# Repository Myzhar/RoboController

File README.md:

RoboController
==============

This project contains the software and firmware developed for RoboController v2 board: http://www.tuttoelettronica.org/?p=455

RobotController v2 is a board created to perform advanced motor control when you need RealTime control of two motors with encoder feedback. 

The RoboController v2 board is used to control MyzharBot robot: http://www.robot-home.it

MODULES
-------

* **HLU** (**H**igh **L**evel **U**nit): the **HLU** folder contains the High Level software, all the software that runs on a CPU (PC, embedded boards, mobile devices)
* **LLU** (**L**ow **L**evel **U**nit): the **LLU** folder contains the Low Level software, "the firmware", that runs on a MCU (Motor control board, sensor boards, IMU)

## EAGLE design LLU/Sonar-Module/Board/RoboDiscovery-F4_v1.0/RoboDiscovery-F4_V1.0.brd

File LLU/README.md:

LLU
===

LOW LEVEL UNIT
--------------

LLU folder contains the Low Level software, all the software that runs on a board powered by a MCU:

* **CPU**: contains the FW code for RoboController v2 board 
* **Sonar-Module**: contains the FW code for STm32F4-Discovery to be suited on RoboDiscovery carrier board

DEVELOPMENT SOFTWARE
--------------------

**Microchip - RoboController v2**
To compile the Firmware to be deployed on RoboController board you need a Microchip programmer (PicKit 3 or ICD 3 are highly suggested) and you need to download the latest version of MPLABX IDE and XC16 from Microchip: https://www.microchip.com/pagehandler/en-us/family/mplabx/

**STm32F4-Discovery**
The Firmware is based on the newest STm32Cube library and it is configured using STm32CubeMX tool.
You will find any further information on www.robodiscovery.com

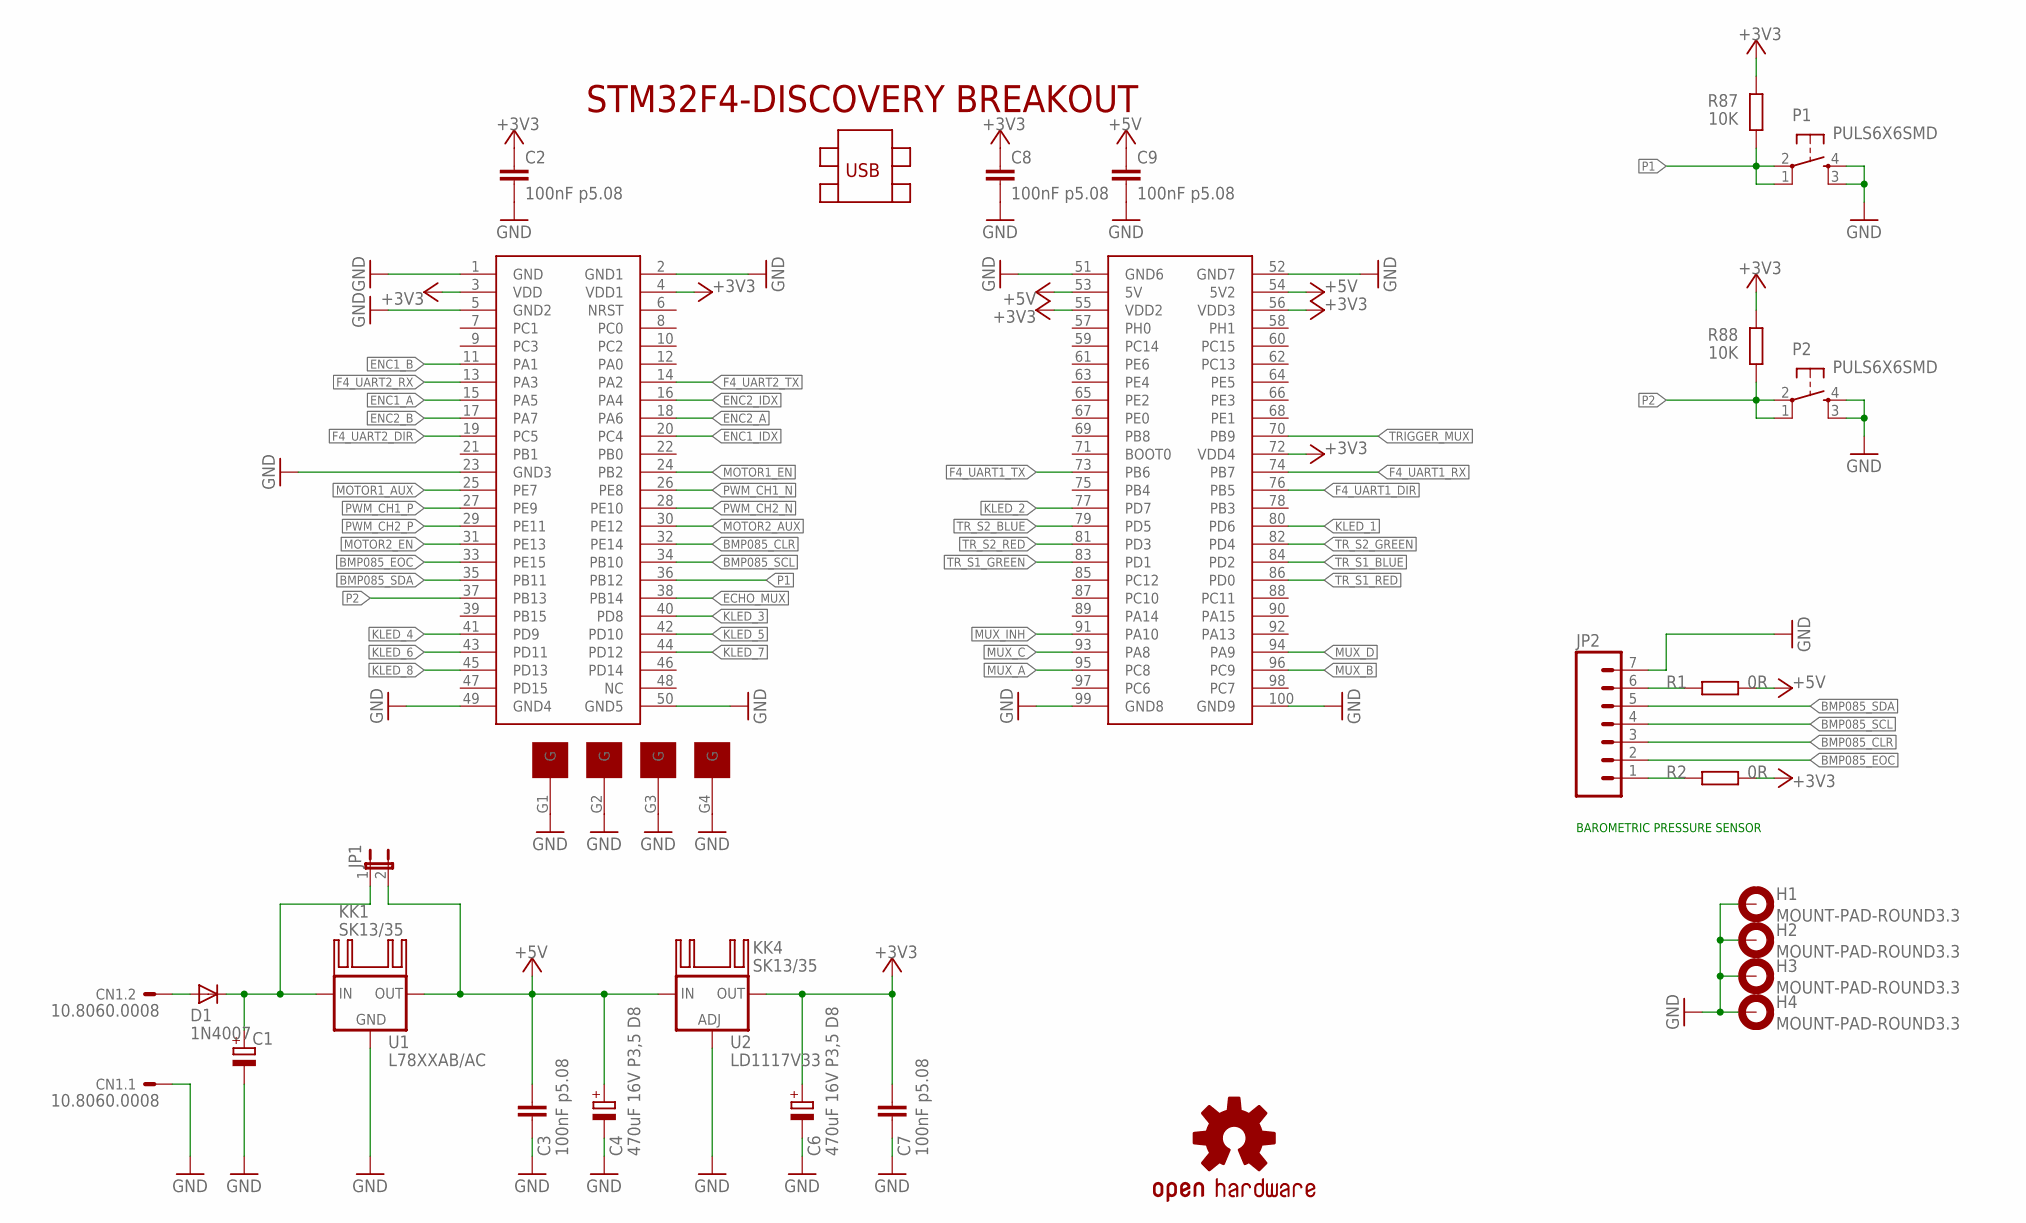
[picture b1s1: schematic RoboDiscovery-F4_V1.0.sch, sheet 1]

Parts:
C1: CPOL-EUE5-13; E5-13
C2, C3, C7, C8, C9: 100nF p5.08; C050-024X044
C4, C6: 470uF 16V P3,5 D8; E3,5-8
CN1: 10.8060.0008; 300-021-13_2P/5VE
D1: 1N4007; D041-10
DIS1: STM32F4-DISCOVERY
H1, H2, H3, H4: MOUNT-PAD-ROUND3.3; 3,3-PAD
JP1: JP1E; JP1
JP2: M07LONGPADS; 1X07_LONGPADS
KK1, KK4: SK13/35
LOGO1: OSHW-LOGOM; OSHW-LOGO-M
P1, P2: PULS6X6SMD
R1, R2: 0R; 0207/7
R87, R88: 10K; 0207/7
U1: L78XXAB/AC; 78XXL
U2: LD1117V33; 317TL

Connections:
+3V3: C2.1, C6.+, C7.1, C8.1, DIS1.3 (VDD), DIS1.4 (VDD1), DIS1.55 (VDD2), DIS1.56 (VDD3), DIS1.72 (VDD4), R2.1, R87.1, R88.1, U2.2 (OUT); also elsewhere on the board
+5V: C3.1, C4.+, C9.1, DIS1.53 (5V), DIS1.54 (5V2), JP1.2, R1.1, U1.OUT, U2.3 (IN); also elsewhere on the board
BMP085_CLR: DIS1.32 (PE14), JP2.3
BMP085_EOC: DIS1.33 (PE15), JP2.2
BMP085_SCL: DIS1.34 (PB10), JP2.4
BMP085_SDA: DIS1.35 (PB11), JP2.5
ECHO_MUX: DIS1.38 (PB14); also elsewhere on the board
ENC1_A: DIS1.15 (PA5); also elsewhere on the board
ENC1_B: DIS1.11 (PA1); also elsewhere on the board
ENC1_IDX: DIS1.20 (PC4); also elsewhere on the board
ENC2_A: DIS1.18 (PA6); also elsewhere on the board
ENC2_B: DIS1.17 (PA7); also elsewhere on the board
ENC2_IDX: DIS1.16 (PA4); also elsewhere on the board
F4_UART1_DIR: DIS1.76 (PB5); also elsewhere on the board
F4_UART1_RX: DIS1.74 (PB7); also elsewhere on the board
F4_UART1_TX: DIS1.73 (PB6); also elsewhere on the board
F4_UART2_DIR: DIS1.19 (PC5); also elsewhere on the board
F4_UART2_RX: DIS1.13 (PA3); also elsewhere on the board
F4_UART2_TX: DIS1.14 (PA2); also elsewhere on the board
GND: C1.-, C2.2, C3.2, C4.-, C6.-, C7.2, C8.2, C9.2, CN1.1, DIS1.1 (GND), DIS1.2 (GND1), DIS1.5 (GND2), DIS1.23 (GND3), DIS1.49 (GND4), DIS1.50 (GND5), DIS1.51 (GND6), DIS1.52 (GND7), DIS1.99 (GND8), DIS1.100 (GND9), DIS1.G1 (G), DIS1.G2 (G), DIS1.G3 (G), DIS1.G4 (G), H1.B3,3, H2.B3,3, H3.B3,3, H4.B3,3, JP2.7, P1.3 (S1), P1.4 (S), P2.3 (S1), P2.4 (S), U1.GND, U2.1 (ADJ); also elsewhere on the board
KLED_1: DIS1.80 (PD6); also elsewhere on the board
KLED_2: DIS1.77 (PD7); also elsewhere on the board
KLED_3: DIS1.40 (PD8); also elsewhere on the board
KLED_4: DIS1.41 (PD9); also elsewhere on the board
KLED_5: DIS1.42 (PD10); also elsewhere on the board
KLED_6: DIS1.43 (PD11); also elsewhere on the board
KLED_7: DIS1.44 (PD12); also elsewhere on the board
KLED_8: DIS1.45 (PD13); also elsewhere on the board
MOTOR1_AUX: DIS1.25 (PE7); also elsewhere on the board
MOTOR1_EN: DIS1.24 (PB2); also elsewhere on the board
MOTOR2_AUX: DIS1.30 (PE12); also elsewhere on the board
MOTOR2_EN: DIS1.31 (PE13); also elsewhere on the board
MUX_A: DIS1.95 (PC8); also elsewhere on the board
MUX_B: DIS1.96 (PC9); also elsewhere on the board
MUX_C: DIS1.93 (PA8); also elsewhere on the board
MUX_D: DIS1.94 (PA9); also elsewhere on the board
MUX_INH: DIS1.91 (PA10); also elsewhere on the board
unnamed: C1.+, D1.C, JP1.1, U1.IN
unnamed: JP2.6, R1.2
unnamed: JP2.1, R2.2
unnamed: CN1.2, D1.A
P1: DIS1.36 (PB12), P1.1, P1.2, R87.2
P2: DIS1.37 (PB13), P2.1, P2.2, R88.2
PWM_CH1_N: DIS1.26 (PE8); also elsewhere on the board
PWM_CH1_P: DIS1.27 (PE9); also elsewhere on the board
PWM_CH2_N: DIS1.28 (PE10); also elsewhere on the board
PWM_CH2_P: DIS1.29 (PE11); also elsewhere on the board
TRIGGER_MUX: DIS1.70 (PB9); also elsewhere on the board
TR_S1_BLUE: DIS1.84 (PD2); also elsewhere on the board
TR_S1_GREEN: DIS1.83 (PD1); also elsewhere on the board
TR_S1_RED: DIS1.86 (PD0); also elsewhere on the board
TR_S2_BLUE: DIS1.79 (PD5); also elsewhere on the board
TR_S2_GREEN: DIS1.82 (PD4); also elsewhere on the board
TR_S2_RED: DIS1.81 (PD3); also elsewhere on the board

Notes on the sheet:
BAROMETRIC PRESSURE SENSOR

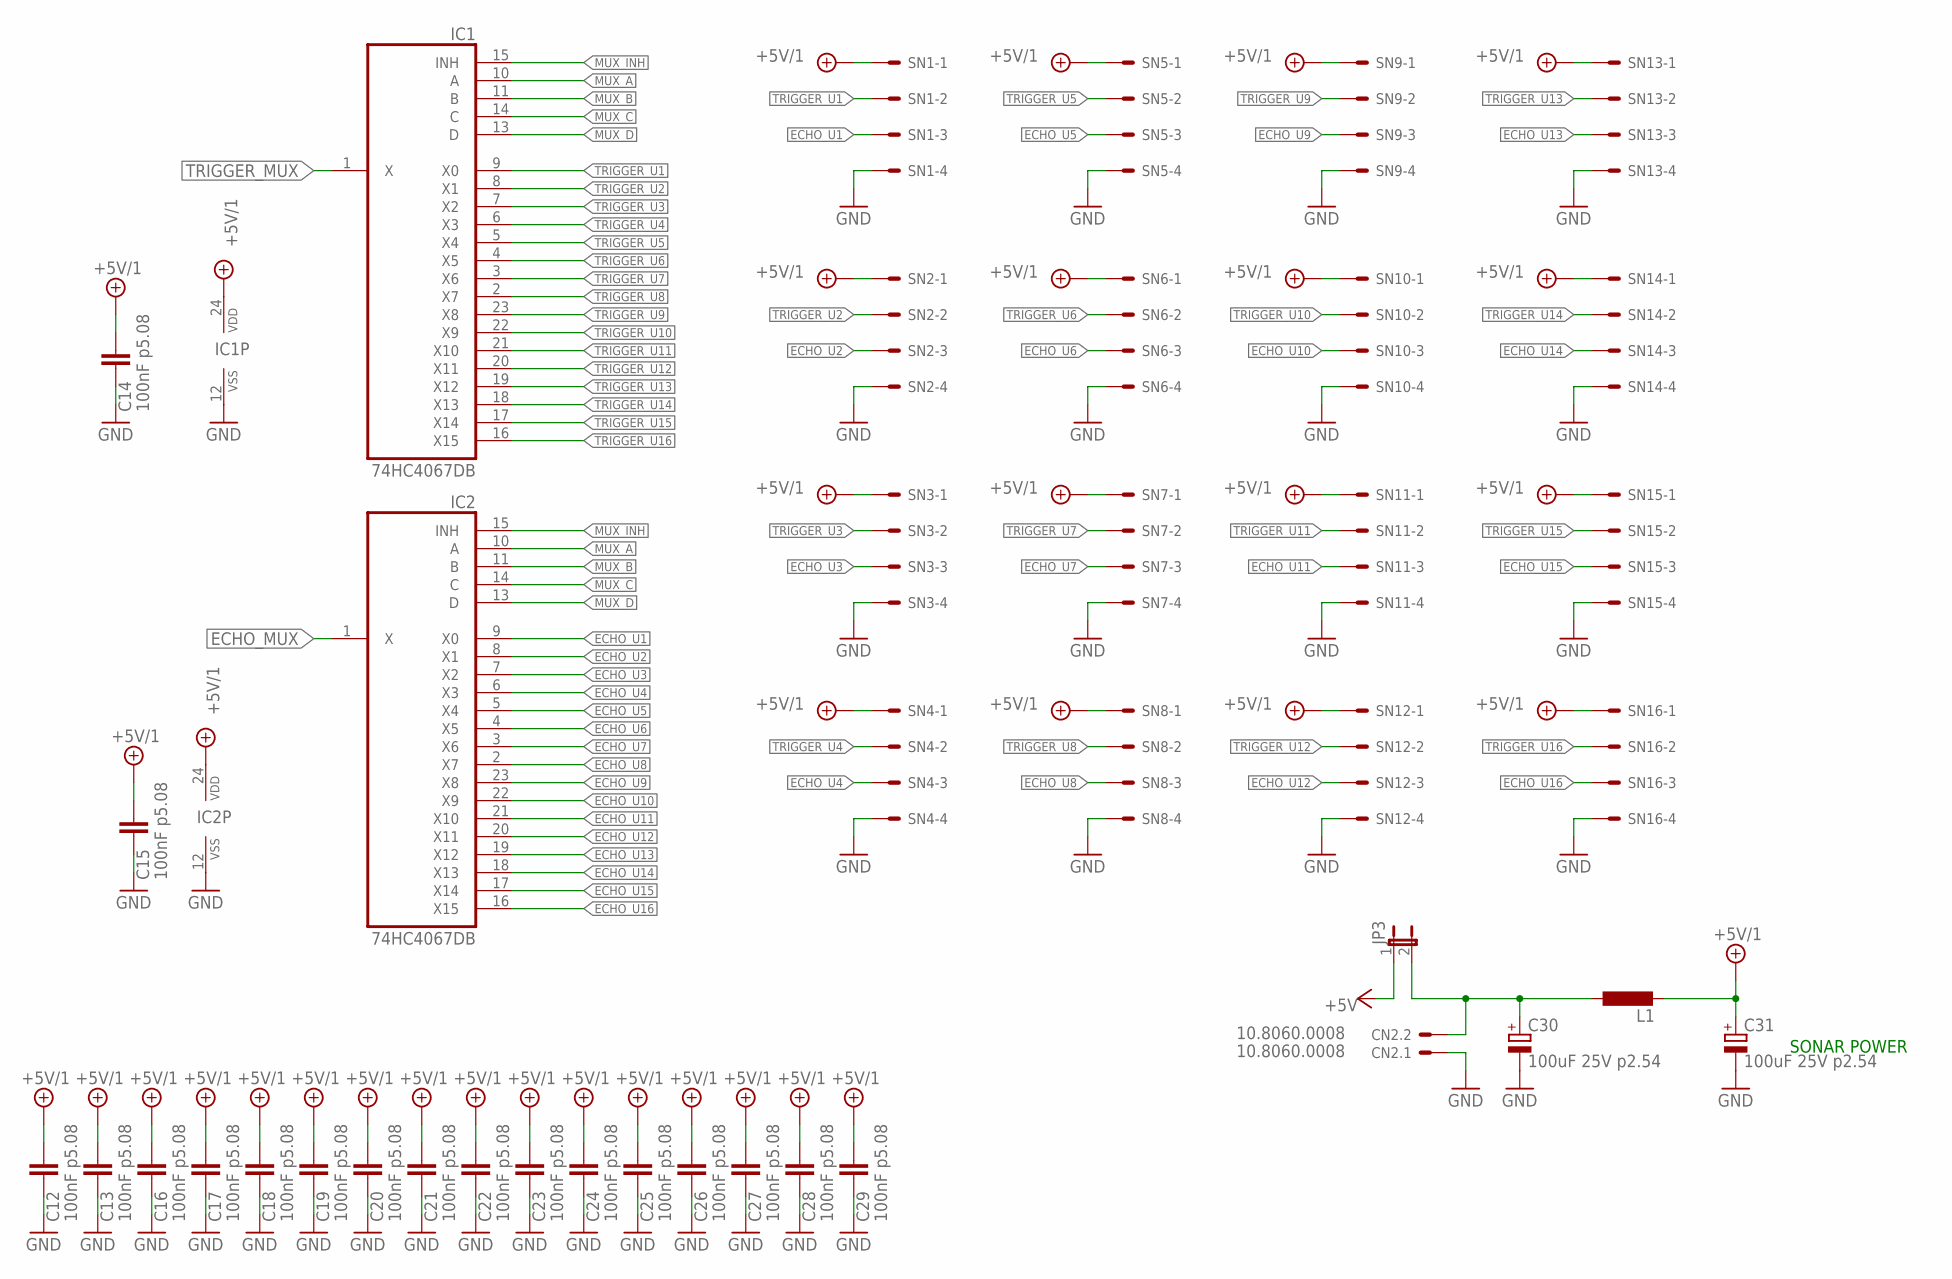
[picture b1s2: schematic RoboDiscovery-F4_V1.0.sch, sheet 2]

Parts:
C12, C13, C14, C15, C16, C17, C18, C19, C20, C21, C22, C23, C24, C25, C26, C27, C28, C29: 100nF p5.08; C050-024X044
C30, C31: 100uF 25V p2.54; E2,5-6
CN2: 10.8060.0008; 300-021-13_2P/5VE
IC1, IC2: 74HC4067DB; SO24W
JP3: JP1E; JP1
L1: L-EU2200-12.7; 2200-12.7
SN1, SN2, SN3, SN4, SN5, SN6, SN7, SN8, SN9, SN10, SN11, SN12, SN13, SN14, SN15, SN16: 22-27-2041-04; 6410-04

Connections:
+5V: JP3.1; also elsewhere on the board
+5V/1: C12.1, C13.1, C14.1, C15.1, C16.1, C17.1, C18.1, C19.1, C20.1, C21.1, C22.1, C23.1, C24.1, C25.1, C26.1, C27.1, C28.1, C29.1, C31.+, IC1.24 (VDD), IC2.24 (VDD), L1.2, SN1.1, SN2.1, SN3.1, SN4.1, SN5.1, SN6.1, SN7.1, SN8.1, SN9.1, SN10.1, SN11.1, SN12.1, SN13.1, SN14.1, SN15.1, SN16.1; also elsewhere on the board
ECHO_MUX: IC2.1 (X); also elsewhere on the board
ECHO_U1: IC2.9 (X0), SN1.3; also elsewhere on the board
ECHO_U2: IC2.8 (X1), SN2.3; also elsewhere on the board
ECHO_U3: IC2.7 (X2), SN3.3; also elsewhere on the board
ECHO_U4: IC2.6 (X3), SN4.3; also elsewhere on the board
ECHO_U5: IC2.5 (X4), SN5.3; also elsewhere on the board
ECHO_U6: IC2.4 (X5), SN6.3; also elsewhere on the board
ECHO_U7: IC2.3 (X6), SN7.3; also elsewhere on the board
ECHO_U8: IC2.2 (X7), SN8.3; also elsewhere on the board
ECHO_U9: IC2.23 (X8), SN9.3; also elsewhere on the board
ECHO_U10: IC2.22 (X9), SN10.3; also elsewhere on the board
ECHO_U11: IC2.21 (X10), SN11.3; also elsewhere on the board
ECHO_U12: IC2.20 (X11), SN12.3; also elsewhere on the board
ECHO_U13: IC2.19 (X12), SN13.3; also elsewhere on the board
ECHO_U14: IC2.18 (X13), SN14.3; also elsewhere on the board
ECHO_U15: IC2.17 (X14), SN15.3; also elsewhere on the board
ECHO_U16: IC2.16 (X15), SN16.3; also elsewhere on the board
GND: C12.2, C13.2, C14.2, C15.2, C16.2, C17.2, C18.2, C19.2, C20.2, C21.2, C22.2, C23.2, C24.2, C25.2, C26.2, C27.2, C28.2, C29.2, C30.-, C31.-, CN2.1, IC1.12 (VSS), IC2.12 (VSS), SN1.4, SN2.4, SN3.4, SN4.4, SN5.4, SN6.4, SN7.4, SN8.4, SN9.4, SN10.4, SN11.4, SN12.4, SN13.4, SN14.4, SN15.4, SN16.4; also elsewhere on the board
MUX_A: IC1.10 (A), IC2.10 (A); also elsewhere on the board
MUX_B: IC1.11 (B), IC2.11 (B); also elsewhere on the board
MUX_C: IC1.14 (C), IC2.14 (C); also elsewhere on the board
MUX_D: IC1.13 (D), IC2.13 (D); also elsewhere on the board
MUX_INH: IC1.15 (INH), IC2.15 (INH); also elsewhere on the board
unnamed: C30.+, CN2.2, JP3.2, L1.1
TRIGGER_MUX: IC1.1 (X); also elsewhere on the board
TRIGGER_U1: IC1.9 (X0), SN1.2; also elsewhere on the board
TRIGGER_U2: IC1.8 (X1), SN2.2; also elsewhere on the board
TRIGGER_U3: IC1.7 (X2), SN3.2; also elsewhere on the board
TRIGGER_U4: IC1.6 (X3), SN4.2; also elsewhere on the board
TRIGGER_U5: IC1.5 (X4), SN5.2; also elsewhere on the board
TRIGGER_U6: IC1.4 (X5), SN6.2; also elsewhere on the board
TRIGGER_U7: IC1.3 (X6), SN7.2; also elsewhere on the board
TRIGGER_U8: IC1.2 (X7), SN8.2; also elsewhere on the board
TRIGGER_U9: IC1.23 (X8), SN9.2; also elsewhere on the board
TRIGGER_U10: IC1.22 (X9), SN10.2; also elsewhere on the board
TRIGGER_U11: IC1.21 (X10), SN11.2; also elsewhere on the board
TRIGGER_U12: IC1.20 (X11), SN12.2; also elsewhere on the board
TRIGGER_U13: IC1.19 (X12), SN13.2; also elsewhere on the board
TRIGGER_U14: IC1.18 (X13), SN14.2; also elsewhere on the board
TRIGGER_U15: IC1.17 (X14), SN15.2; also elsewhere on the board
TRIGGER_U16: IC1.16 (X15), SN16.2; also elsewhere on the board

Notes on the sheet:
SONAR POWER

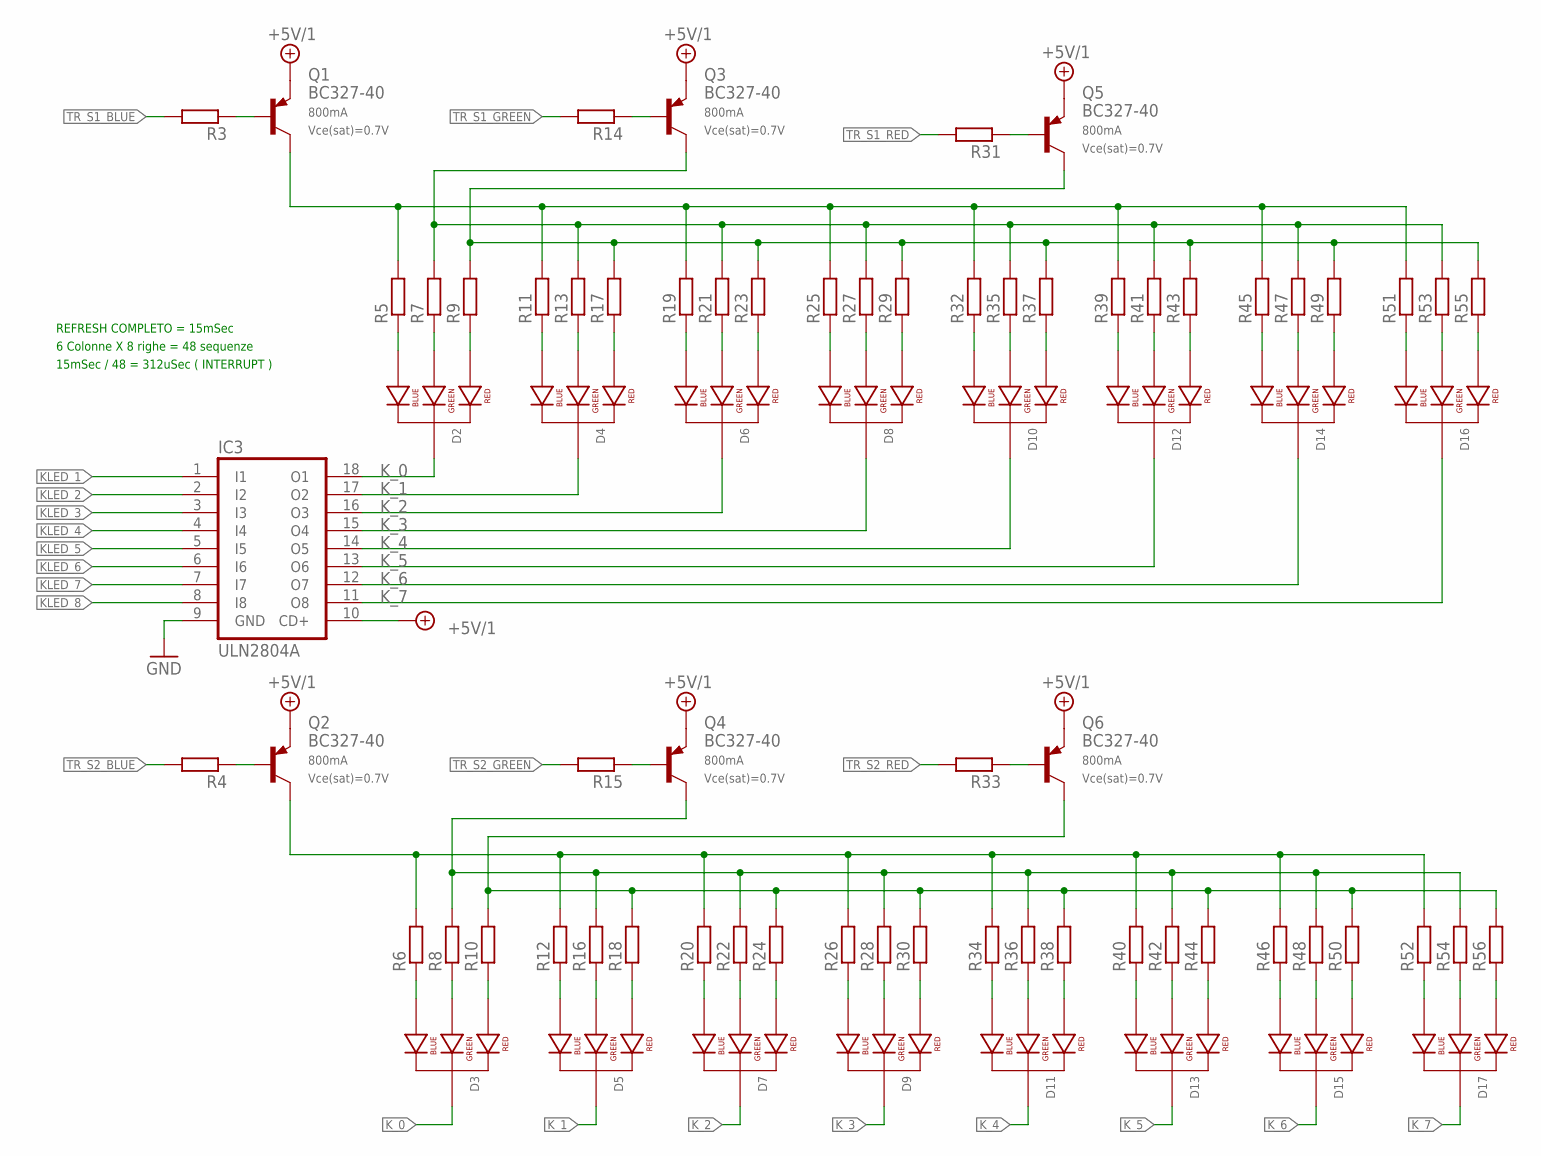
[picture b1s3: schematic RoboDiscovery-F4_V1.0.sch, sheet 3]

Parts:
D2, D3, D4, D5, D6, D7, D8, D9, D10, D11, D12, D13, D14, D15, D16, D17: LED-RGB-CC-THRUDIFFUSE; LED-RGB-THRU
IC3: ULN2804A; DIL18
Q1, Q2, Q3, Q4, Q5, Q6: BC327-40; TO92-EBC
R3, R4, R5, R6, R7, R8, R9, R10, R11, R12, R13, R14, R15, R16, R17, R18, R19, R20, R21, R22, R23, R24, R25, R26, R27, R28, R29, R30, R31, R32, R33, R34, R35, R36, R37, R38, R39, R40, R41, R42, R43, R44, R45, R46, R47, R48, R49, R50, R51, R52, R53, R54, R55, R56: R-EU_0207/7; 0207/7

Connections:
+5V/1: IC3.10 (CD+), Q1.E, Q2.E, Q3.E, Q4.E, Q5.E, Q6.E; also elsewhere on the board
GND: IC3.9 (GND); also elsewhere on the board
KLED_1: IC3.1 (I1); also elsewhere on the board
KLED_2: IC3.2 (I2); also elsewhere on the board
KLED_3: IC3.3 (I3); also elsewhere on the board
KLED_4: IC3.4 (I4); also elsewhere on the board
KLED_5: IC3.5 (I5); also elsewhere on the board
KLED_6: IC3.6 (I6); also elsewhere on the board
KLED_7: IC3.7 (I7); also elsewhere on the board
KLED_8: IC3.8 (I8); also elsewhere on the board
K_0: D2.2 (CATHODE), D3.2 (CATHODE), IC3.18 (O1)
K_1: D4.2 (CATHODE), D5.2 (CATHODE), IC3.17 (O2)
K_2: D6.2 (CATHODE), D7.2 (CATHODE), IC3.16 (O3)
K_3: D8.2 (CATHODE), D9.2 (CATHODE), IC3.15 (O4)
K_4: D10.2 (CATHODE), D11.2 (CATHODE), IC3.14 (O5)
K_5: D12.2 (CATHODE), D13.2 (CATHODE), IC3.13 (O6)
K_6: D14.2 (CATHODE), D15.2 (CATHODE), IC3.12 (O7)
K_7: D16.2 (CATHODE), D17.2 (CATHODE), IC3.11 (O8)
unnamed: Q1.C, R5.2, R11.2, R19.2, R25.2, R32.2, R39.2, R45.2, R51.2
unnamed: Q3.C, R7.2, R13.2, R21.2, R27.2, R35.2, R41.2, R47.2, R53.2
unnamed: Q5.C, R9.2, R17.2, R23.2, R29.2, R37.2, R43.2, R49.2, R55.2
unnamed: D2.4 (BLUE_CATHODE), R5.1
unnamed: D2.3 (GREEN_CATHODE), R7.1
unnamed: D2.1 (RED_CATHODE), R9.1
unnamed: D4.4 (BLUE_CATHODE), R11.1
unnamed: D4.3 (GREEN_CATHODE), R13.1
unnamed: D4.1 (RED_CATHODE), R17.1
unnamed: D6.4 (BLUE_CATHODE), R19.1
unnamed: D6.3 (GREEN_CATHODE), R21.1
unnamed: D6.1 (RED_CATHODE), R23.1
unnamed: D8.4 (BLUE_CATHODE), R25.1
unnamed: D8.3 (GREEN_CATHODE), R27.1
unnamed: D8.1 (RED_CATHODE), R29.1
unnamed: D10.4 (BLUE_CATHODE), R32.1
unnamed: D10.3 (GREEN_CATHODE), R35.1
unnamed: D10.1 (RED_CATHODE), R37.1
unnamed: D12.4 (BLUE_CATHODE), R39.1
unnamed: D12.3 (GREEN_CATHODE), R41.1
unnamed: D12.1 (RED_CATHODE), R43.1
unnamed: D14.4 (BLUE_CATHODE), R45.1
unnamed: D14.3 (GREEN_CATHODE), R47.1
unnamed: D14.1 (RED_CATHODE), R49.1
unnamed: D16.4 (BLUE_CATHODE), R51.1
unnamed: D16.3 (GREEN_CATHODE), R53.1
unnamed: D16.1 (RED_CATHODE), R55.1
unnamed: Q2.C, R6.2, R12.2, R20.2, R26.2, R34.2, R40.2, R46.2, R52.2
unnamed: Q4.C, R8.2, R16.2, R22.2, R28.2, R36.2, R42.2, R48.2, R54.2
unnamed: Q6.C, R10.2, R18.2, R24.2, R30.2, R38.2, R44.2, R50.2, R56.2
unnamed: D3.4 (BLUE_CATHODE), R6.1
unnamed: D3.3 (GREEN_CATHODE), R8.1
unnamed: D3.1 (RED_CATHODE), R10.1
unnamed: D5.4 (BLUE_CATHODE), R12.1
unnamed: D5.3 (GREEN_CATHODE), R16.1
unnamed: D5.1 (RED_CATHODE), R18.1
unnamed: D7.4 (BLUE_CATHODE), R20.1
unnamed: D7.3 (GREEN_CATHODE), R22.1
unnamed: D7.1 (RED_CATHODE), R24.1
unnamed: D9.4 (BLUE_CATHODE), R26.1
unnamed: D9.3 (GREEN_CATHODE), R28.1
unnamed: D9.1 (RED_CATHODE), R30.1
unnamed: D11.4 (BLUE_CATHODE), R34.1
unnamed: D11.3 (GREEN_CATHODE), R36.1
unnamed: D11.1 (RED_CATHODE), R38.1
unnamed: D13.4 (BLUE_CATHODE), R40.1
unnamed: D13.3 (GREEN_CATHODE), R42.1
unnamed: D13.1 (RED_CATHODE), R44.1
unnamed: D15.4 (BLUE_CATHODE), R46.1
unnamed: D15.3 (GREEN_CATHODE), R48.1
unnamed: D15.1 (RED_CATHODE), R50.1
unnamed: D17.4 (BLUE_CATHODE), R52.1
unnamed: D17.3 (GREEN_CATHODE), R54.1
unnamed: D17.1 (RED_CATHODE), R56.1
unnamed: Q1.B, R3.1
unnamed: Q3.B, R14.1
unnamed: Q5.B, R31.1
unnamed: Q2.B, R4.1
unnamed: Q4.B, R15.1
unnamed: Q6.B, R33.1
TR_S1_BLUE: R3.2; also elsewhere on the board
TR_S1_GREEN: R14.2; also elsewhere on the board
TR_S1_RED: R31.2; also elsewhere on the board
TR_S2_BLUE: R4.2; also elsewhere on the board
TR_S2_GREEN: R15.2; also elsewhere on the board
TR_S2_RED: R33.2; also elsewhere on the board

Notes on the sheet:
REFRESH COMPLETO = 15mSec
6 Colonne X 8 righe = 48 sequenze
15mSec / 48 = 312uSec ( INTERRUPT )

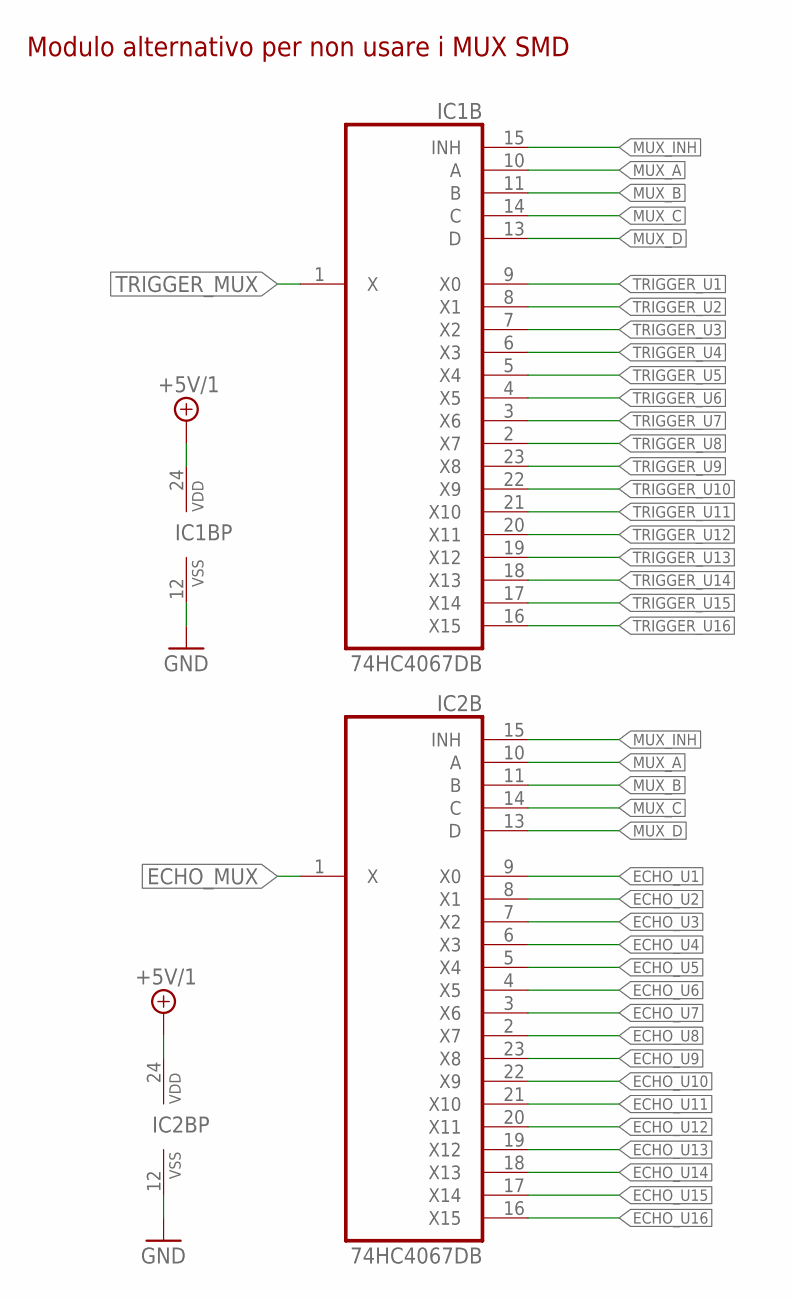
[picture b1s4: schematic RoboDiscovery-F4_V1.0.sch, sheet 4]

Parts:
IC1B, IC2B: 74HC4067DB; DIL24-6

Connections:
+5V/1: IC1B.24 (VDD), IC2B.24 (VDD); also elsewhere on the board
ECHO_MUX: IC2B.1 (X); also elsewhere on the board
ECHO_U1: IC2B.9 (X0); also elsewhere on the board
ECHO_U2: IC2B.8 (X1); also elsewhere on the board
ECHO_U3: IC2B.7 (X2); also elsewhere on the board
ECHO_U4: IC2B.6 (X3); also elsewhere on the board
ECHO_U5: IC2B.5 (X4); also elsewhere on the board
ECHO_U6: IC2B.4 (X5); also elsewhere on the board
ECHO_U7: IC2B.3 (X6); also elsewhere on the board
ECHO_U8: IC2B.2 (X7); also elsewhere on the board
ECHO_U9: IC2B.23 (X8); also elsewhere on the board
ECHO_U10: IC2B.22 (X9); also elsewhere on the board
ECHO_U11: IC2B.21 (X10); also elsewhere on the board
ECHO_U12: IC2B.20 (X11); also elsewhere on the board
ECHO_U13: IC2B.19 (X12); also elsewhere on the board
ECHO_U14: IC2B.18 (X13); also elsewhere on the board
ECHO_U15: IC2B.17 (X14); also elsewhere on the board
ECHO_U16: IC2B.16 (X15); also elsewhere on the board
GND: IC1B.12 (VSS), IC2B.12 (VSS); also elsewhere on the board
MUX_A: IC1B.10 (A), IC2B.10 (A); also elsewhere on the board
MUX_B: IC1B.11 (B), IC2B.11 (B); also elsewhere on the board
MUX_C: IC1B.14 (C), IC2B.14 (C); also elsewhere on the board
MUX_D: IC1B.13 (D), IC2B.13 (D); also elsewhere on the board
MUX_INH: IC1B.15 (INH), IC2B.15 (INH); also elsewhere on the board
TRIGGER_MUX: IC1B.1 (X); also elsewhere on the board
TRIGGER_U1: IC1B.9 (X0); also elsewhere on the board
TRIGGER_U2: IC1B.8 (X1); also elsewhere on the board
TRIGGER_U3: IC1B.7 (X2); also elsewhere on the board
TRIGGER_U4: IC1B.6 (X3); also elsewhere on the board
TRIGGER_U5: IC1B.5 (X4); also elsewhere on the board
TRIGGER_U6: IC1B.4 (X5); also elsewhere on the board
TRIGGER_U7: IC1B.3 (X6); also elsewhere on the board
TRIGGER_U8: IC1B.2 (X7); also elsewhere on the board
TRIGGER_U9: IC1B.23 (X8); also elsewhere on the board
TRIGGER_U10: IC1B.22 (X9); also elsewhere on the board
TRIGGER_U11: IC1B.21 (X10); also elsewhere on the board
TRIGGER_U12: IC1B.20 (X11); also elsewhere on the board
TRIGGER_U13: IC1B.19 (X12); also elsewhere on the board
TRIGGER_U14: IC1B.18 (X13); also elsewhere on the board
TRIGGER_U15: IC1B.17 (X14); also elsewhere on the board
TRIGGER_U16: IC1B.16 (X15); also elsewhere on the board

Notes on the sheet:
Modulo alternativo per non usare i MUX SMD

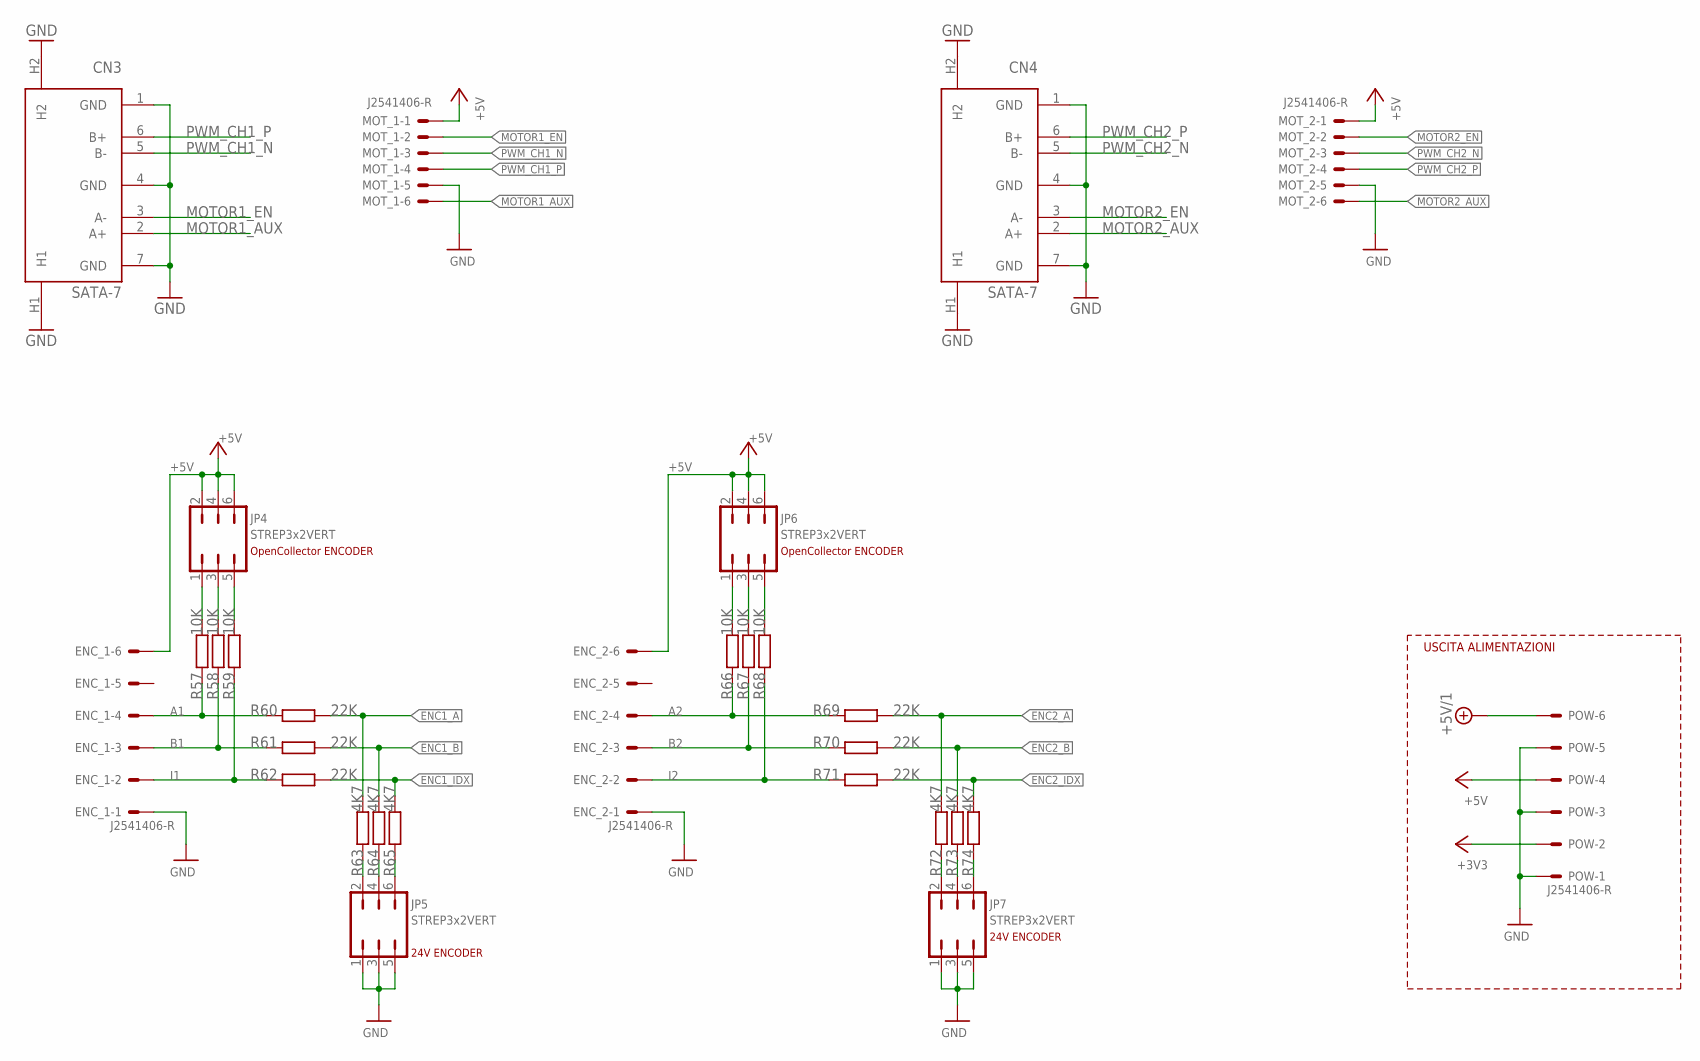
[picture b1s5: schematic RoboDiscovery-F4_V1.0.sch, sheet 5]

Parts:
CN3, CN4: SATA-7; SATA-5607-5102-SH
ENC_1, ENC_2: J2541406-R; 6410-06
JP4, JP5, JP6, JP7: STREP3x2VERT; JP3Q
MOT_1, MOT_2: J2541406-R; 6410-06
POW: J2541406-R; 6410-06
R57, R58, R59, R66, R67, R68: 10K; 0207/7
R60, R61, R62, R69, R70, R71: 22K; 0207/7
R63, R64, R65, R72, R73, R74: 4K7; 0207/7

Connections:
+3V3: POW.2; also elsewhere on the board
+5V: ENC_1.6, ENC_2.6, JP4.2, JP4.4, JP4.6, JP6.2, JP6.4, JP6.6, MOT_1.1, MOT_2.1, POW.4; also elsewhere on the board
+5V/1: POW.6; also elsewhere on the board
A1: ENC_1.4, R57.1, R60.2
A2: ENC_2.4, R66.1, R69.2
B1: ENC_1.3, R58.1, R61.2
B2: ENC_2.3, R67.1, R70.2
ENC1_A: R60.1, R63.2; also elsewhere on the board
ENC1_B: R61.1, R64.2; also elsewhere on the board
ENC1_IDX: R62.1, R65.2; also elsewhere on the board
ENC2_A: R69.1, R72.2; also elsewhere on the board
ENC2_B: R70.1, R73.2; also elsewhere on the board
ENC2_IDX: R71.1, R74.2; also elsewhere on the board
GND: CN3.1 (GND), CN3.4 (GND), CN3.7 (GND), CN3.H1, CN3.H2, CN4.1 (GND), CN4.4 (GND), CN4.7 (GND), CN4.H1, CN4.H2, ENC_1.1, ENC_2.1, JP5.1, JP5.3, JP5.5, JP7.1, JP7.3, JP7.5, MOT_1.5, MOT_2.5, POW.1, POW.3, POW.5; also elsewhere on the board
I1: ENC_1.2, R59.1, R62.2
I2: ENC_2.2, R68.1, R71.2
MOTOR1_AUX: CN3.2 (A+), MOT_1.6; also elsewhere on the board
MOTOR1_EN: CN3.3 (A-), MOT_1.2; also elsewhere on the board
MOTOR2_AUX: CN4.2 (A+), MOT_2.6; also elsewhere on the board
MOTOR2_EN: CN4.3 (A-), MOT_2.2; also elsewhere on the board
unnamed: JP6.3, R67.2
unnamed: JP6.5, R68.2
unnamed: JP6.1, R66.2
unnamed: JP4.3, R58.2
unnamed: JP4.5, R59.2
unnamed: JP4.1, R57.2
unnamed: JP5.2, R63.1
unnamed: JP5.4, R64.1
unnamed: JP5.6, R65.1
unnamed: JP7.2, R72.1
unnamed: JP7.4, R73.1
unnamed: JP7.6, R74.1
PWM_CH1_N: CN3.5 (B-), MOT_1.3; also elsewhere on the board
PWM_CH1_P: CN3.6 (B+), MOT_1.4; also elsewhere on the board
PWM_CH2_N: CN4.5 (B-), MOT_2.3; also elsewhere on the board
PWM_CH2_P: CN4.6 (B+), MOT_2.4; also elsewhere on the board

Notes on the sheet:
USCITA ALIMENTAZIONI
24V ENCODER
OpenCollector ENCODER

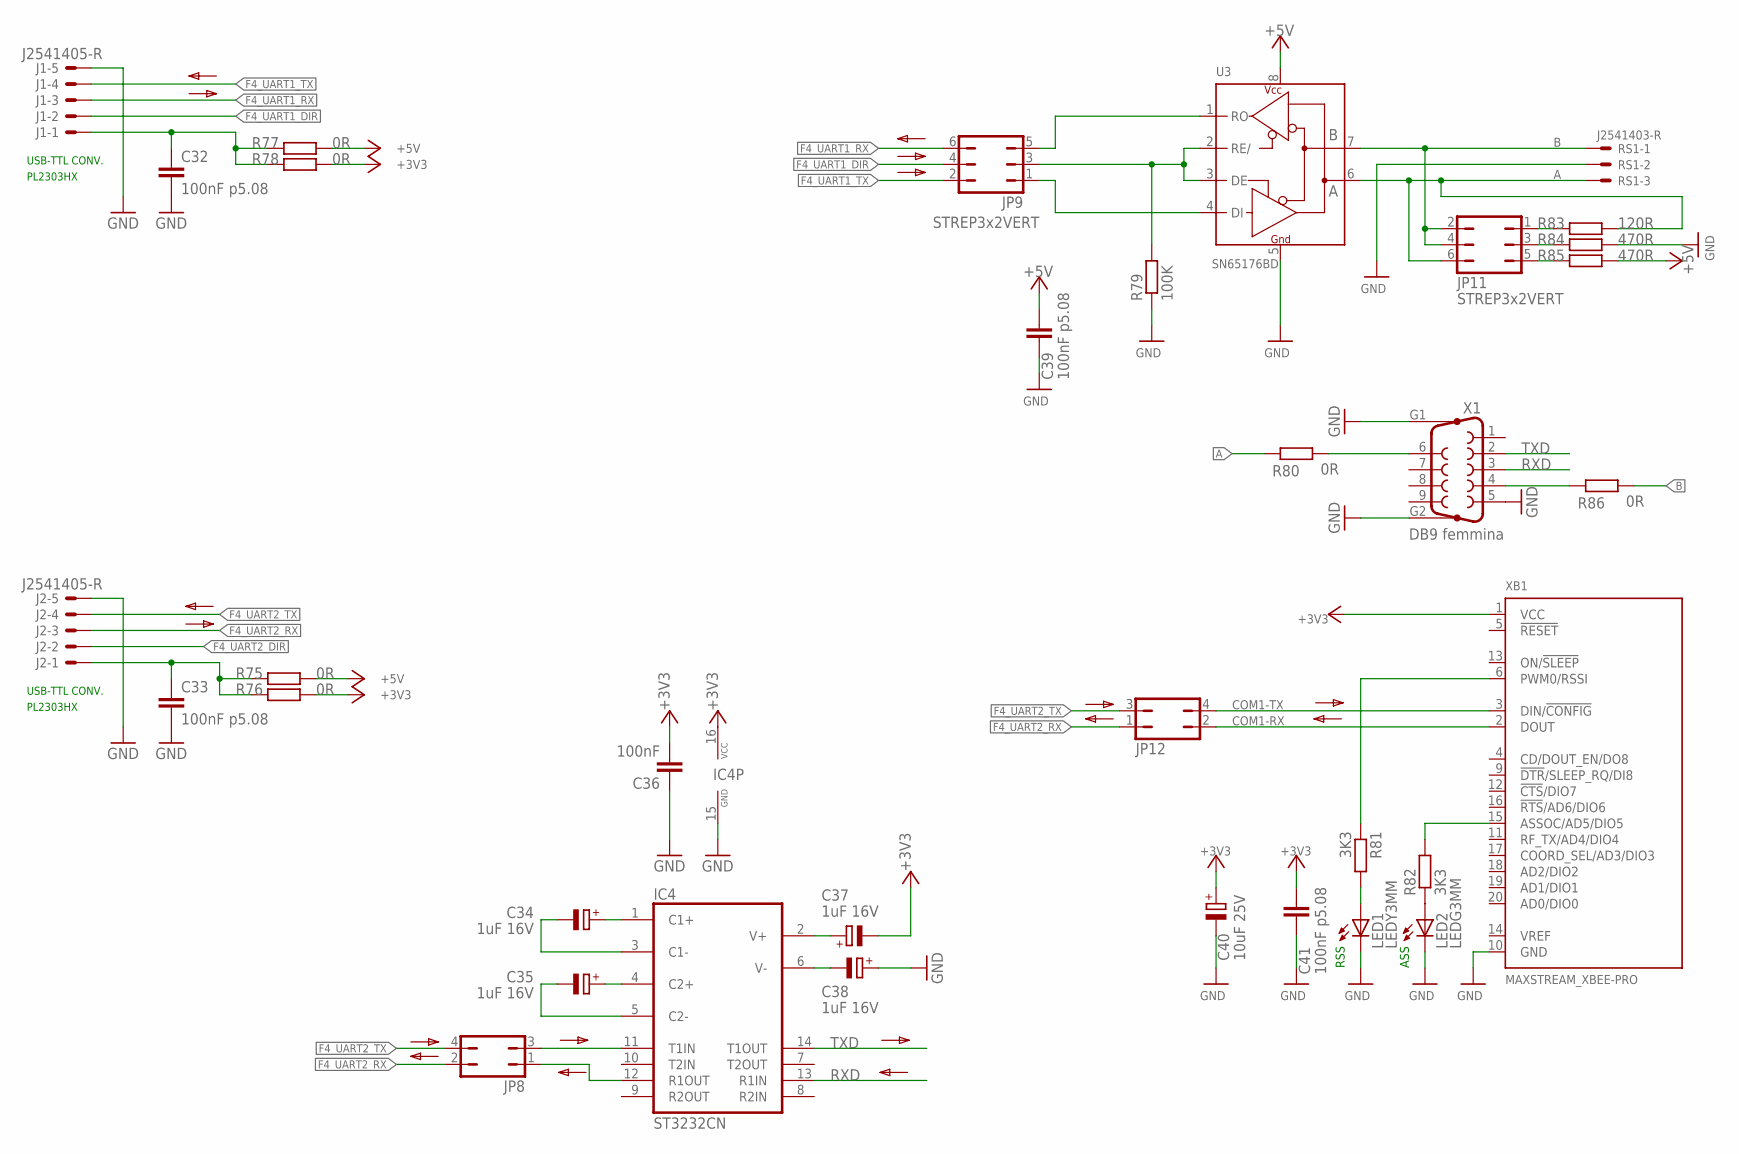
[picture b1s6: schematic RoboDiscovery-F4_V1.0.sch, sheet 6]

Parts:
C32, C33, C39, C41: 100nF p5.08; C050-024X044
C34, C35, C37, C38: 1uF 16V; E2,5-5
C36: 100nF; C025-025X050
C40: 10uF 25V; E2,5-5
IC4: ST3232CN; DIL16
J1, J2: J2541405-R; 6410-05
JP8, JP12: JP2Q
JP9, JP11: STREP3x2VERT; JP3Q
LED1: LEDY3MM; LED3MM
LED2: LEDG3MM; LED3MM
R75, R76, R77, R78, R80, R86: 0R; 0207/7
R79: 100K; 0207/7
R81, R82: 3K3; 0207/7
R83: 120R; 0207/7
R84, R85: 470R; 0207/7
RS1: J2541403-R; 6410-03
U3: SN65176BD; DIL8
X1: DB9 femmina; F09HP
XB1: MAXSTREAM_XBEE-PRO

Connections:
+3V3: C36.2, C37.-, C40.+, C41.1, IC4.16 (VCC), R76.1, R78.1, XB1.1 (VCC); also elsewhere on the board
+5V: C39.1, R75.1, R77.1, R85.1, U3.8 (VCC); also elsewhere on the board
A: JP11.6, R80.2, R83.1, RS1.3, U3.6 (A)
B: JP11.2, JP11.4, R86.1, RS1.1, U3.7 (B)
COM1-RX: JP12.2, XB1.2 (DOUT)
COM1-TX: JP12.4, XB1.3 (DIN/!CONFIG)
F4_UART1_DIR: J1.2, JP9.4; also elsewhere on the board
F4_UART1_RX: J1.3, JP9.6; also elsewhere on the board
F4_UART1_TX: J1.4, JP9.2; also elsewhere on the board
F4_UART2_DIR: J2.2; also elsewhere on the board
F4_UART2_RX: J2.3, JP8.2, JP12.1; also elsewhere on the board
F4_UART2_TX: J2.4, JP8.4, JP12.3; also elsewhere on the board
GND: C32.2, C33.2, C36.1, C38.+, C39.2, C40.-, C41.2, IC4.15 (GND), J1.5, J2.5, LED1.K (C), LED2.K (C), R79.1, R84.2, RS1.2, U3.5 (GND), X1.5, X1.G1, X1.G2, XB1.10 (GND); also elsewhere on the board
unnamed: C33.1, J2.1, R75.2, R76.2
unnamed: R82.2, XB1.15 (ASSOC/AD5/DIO5)
unnamed: LED2.A, R82.1
unnamed: LED1.A, R81.2
unnamed: R81.1, XB1.6 (PWM0/RSSI)
unnamed: R80.1, X1.6
unnamed: C32.1, J1.1, R77.2, R78.2
unnamed: JP11.3, R84.1
unnamed: JP11.5, R85.2
unnamed: JP11.1, R83.2
unnamed: C35.-, IC4.5 (C2-)
unnamed: C34.-, IC4.3 (C1-)
unnamed: C34.+, IC4.1 (C1+)
unnamed: C35.+, IC4.4 (C2+)
unnamed: C38.-, IC4.6 (V-)
unnamed: C37.+, IC4.2 (V+)
unnamed: IC4.11 (T1IN), JP8.3
unnamed: IC4.12 (R1OUT), JP8.1
unnamed: JP9.5, U3.1 (RO)
unnamed: R86.2, X1.4
RS-DIR: JP9.3, R79.2, U3.2 (RE/), U3.3 (DE)
RS-TX: JP9.1, U3.4 (DI)
RXD: IC4.13 (R1IN), X1.3
TXD: IC4.14 (T1OUT), X1.2

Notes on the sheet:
USB-TTL CONV.
PL2303HX
RSS
ASS

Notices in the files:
parts and their libraries:
SparkFun-Connectors: Licensing: Creative Commons ShareAlike 4.0 International - https://creativecommons.org/licenses/by-sa/4.0
